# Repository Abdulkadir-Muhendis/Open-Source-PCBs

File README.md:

# Open-Source-PCBs
Open Source Printed Circuit Boards
----------------------------------

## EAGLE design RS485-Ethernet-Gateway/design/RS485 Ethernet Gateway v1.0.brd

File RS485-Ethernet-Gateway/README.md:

==========================================================================================================================================
# Next revision of this project is a part of upcoming crowdfunding campaign. Details [here](https://www.crowdsupply.com/domatic/getwired).
==========================================================================================================================================

## RS485 Module Family
This is ethernet gateway for RS485 (wired) MySensors nodes. It features ATmega328p MCU and ENC28J60 ethernet chip. SP485EE or similar IC is used as RS485 transceiver. It works on hardware serial to ensure more stability and to achieve higher baud rates.

The board itself is designed with having thermal issues in mind, since the ENC28J60 draws a lot of current. It features two 10-pin IDC sockets, one to connect external PCB with LEDs (Power, TX, RX, Error) and RESET button, and one for programming (MOSI, MISO, SCK, TX, RX, 5V, GND). Its size makes it case compatible with Raspberry Pi.

This work is a part of our [RS485 module system](https://www.openhardware.io/view/639/RS485-MCU-Module).

## Technical Specification
- ATmega328p MCU,
- ENC28J60 10Base-T ethernet controller,
- SP485EE for RS485 wired bus communication (working on hardware serial, pin 0 & 1),
- Shielded RJ45 socket with LEDs,
- 10-pin IDC socket for firmware updates and debugging,
- 10-pin IDC socket to connect external PCB with LEDs and a button (Power, TX, RX, Error, RESET),
- 5V and 3.3 V voltage regulators on board with large cooling pads,
- Power consumption < 2 W,
- Doubled outputs for RS485 bus connection (to connect the gateway easily in the middle of the bus).

## Q&A
We will place typical questions and answers here, if they occur.

## Firmware
- [Github](https://github.com/feanor-anglin/RS485)

## Our other RS485 boards
- [RS485 MCU Module](https://www.openhardware.io/view/639/RS485-MCU-Module)
- [RS485 2SSR Shield](https://www.openhardware.io/view/640/RS485-2SSR-Shield)
- [RS485 4RelayDin Shield](https://www.openhardware.io/view/641/RS485-4RelayDin-Shield)

## Other information
Copyright feanor-anglin (2018). Released under the [CERN Open Hardware Licence v1.2](http://ohwr.org/cernohl)

We develop Arduino compatibile hardware for wired home automation systems. If you like what we do and want us to keep going, please donate!

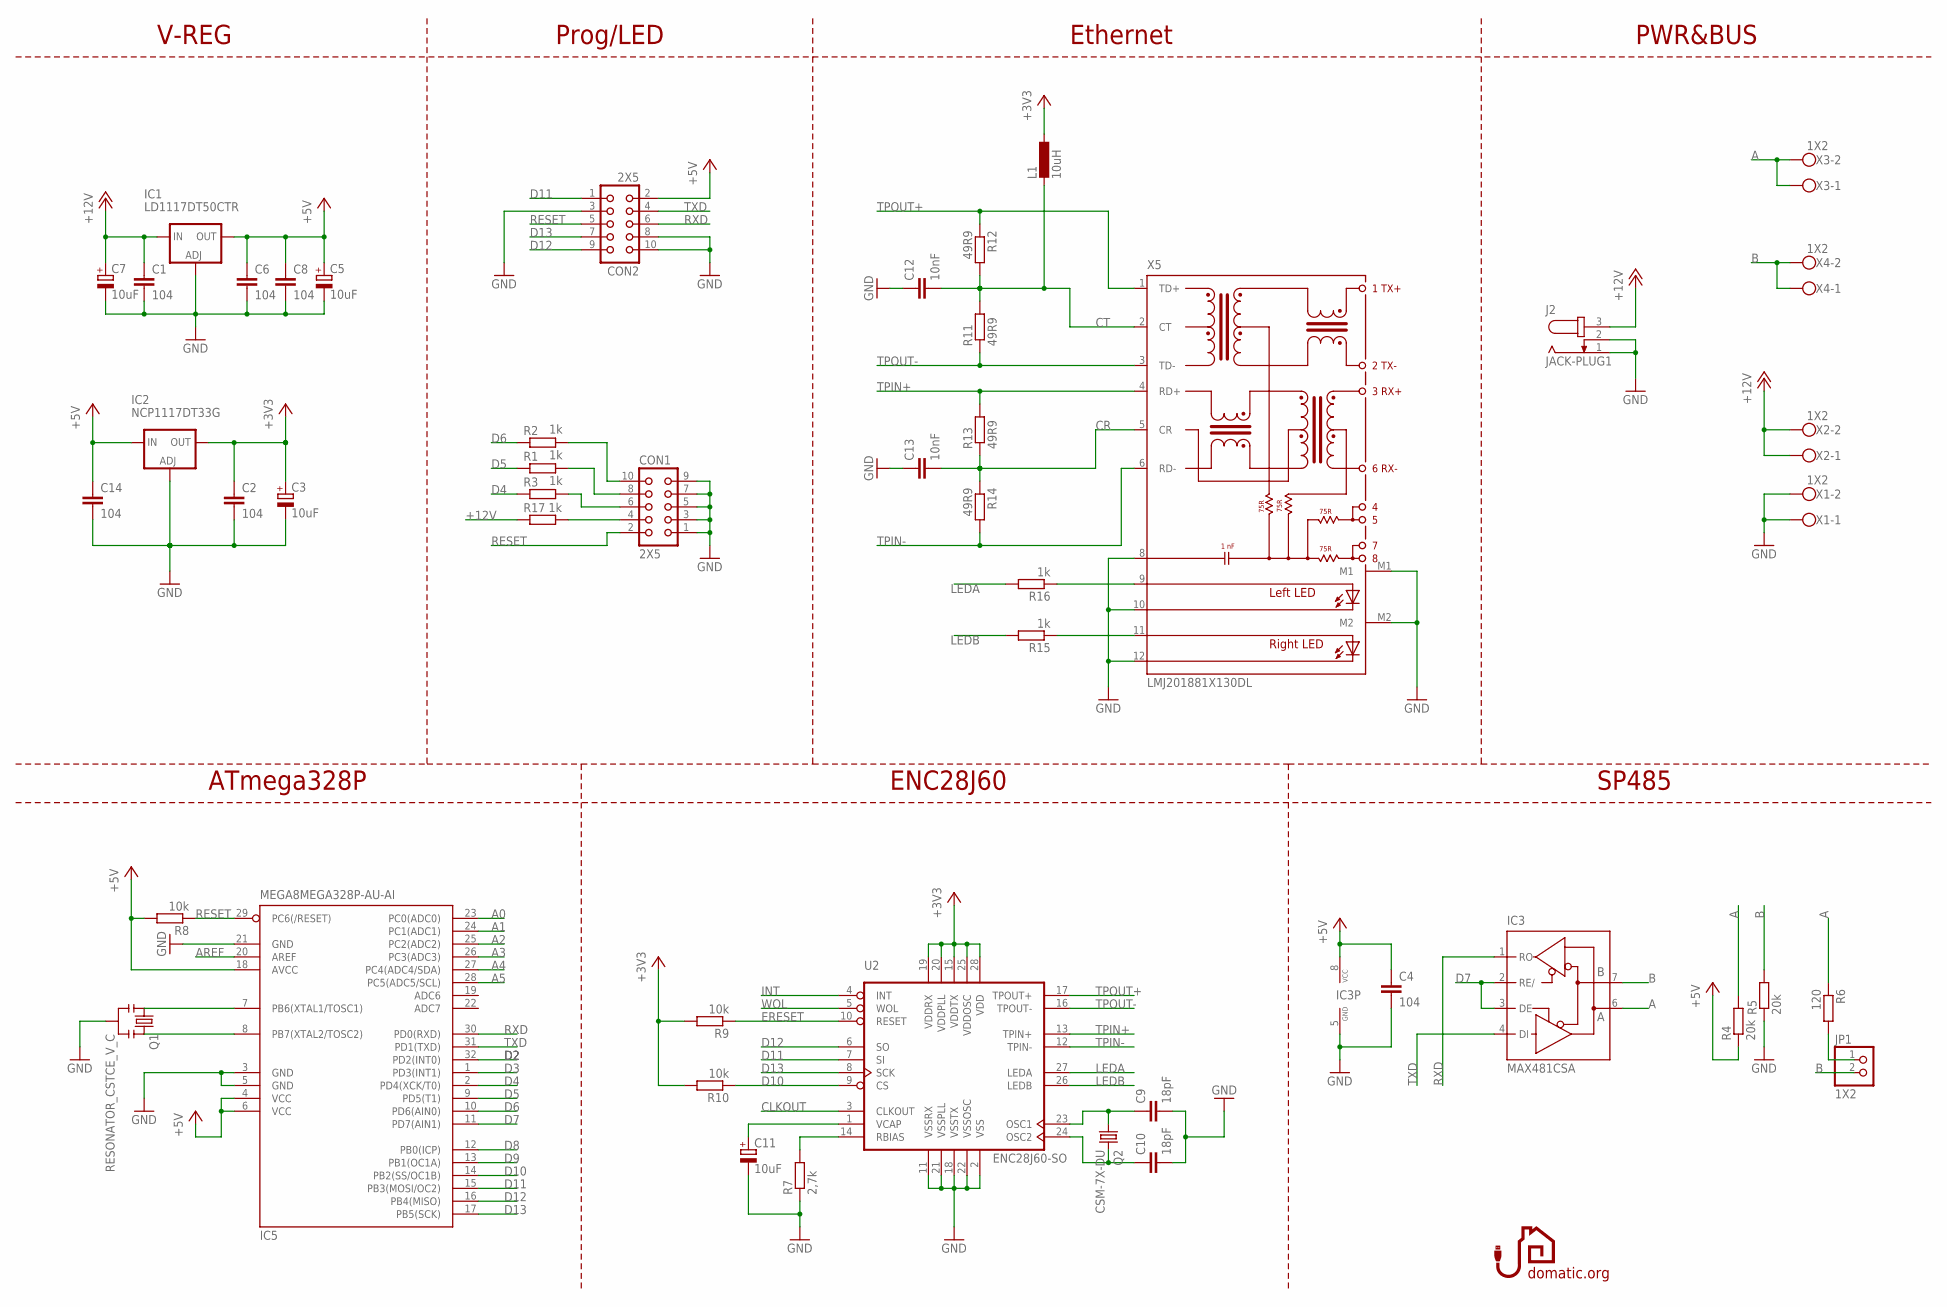
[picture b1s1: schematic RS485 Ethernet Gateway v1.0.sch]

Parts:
C1, C2, C4, C6, C8, C14: 104; C0603
C3, C5, C7, C11: 10uF; E2,5-7
C9, C10: 18pF; C0603
C12, C13: 10nF; C0603
CON1, CON2: 2X5; CON10L
IC1: LD1117DT50CTR; DPACK
IC2: NCP1117DT33G; DPACK
IC3: MAX481CSA; SO08
IC5: MEGA8MEGA328P-AU-AI; TQFP32-08
J2: JACK-PLUG1; SPC4078
JP1: 1X2; 1X02
L1: 10uH; C1608
Q1: RESONATOR_CSTCE_V_C; CSTCE_V_C
Q2: CSM-7X-DU
R1, R2, R3, R15, R16, R17: 1k; R0603
R4, R5: 20k; R0603
R6: 120; R0603
R7: 2,7k; R0603
R8, R9, R10: 10k; R0603
R11, R12, R13, R14: 49R9; R0603
U2: ENC28J60-SO; SO28W
X1, X2, X3, X4: 1X2; W237-102
X5: LMJ201881X130DL; LMJ20188X130

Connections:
+3V3: C2.1, C3.+, IC2.4 (OUT), L1.1, R9.2, R10.2, U2.15 (VDDTX), U2.19 (VDDRX), U2.20 (VDDPLL), U2.25 (VDDOSC), U2.28 (VDD)
+5V: C4.1, C5.+, C6.1, C8.1, C14.1, CON2.2, IC1.4 (OUT), IC2.3 (IN), IC3.8 (VCC), IC5.4 (VCC), IC5.6 (VCC), IC5.18 (AVCC), R4.1, R8.2
+12V: C1.1, C7.+, IC1.3 (IN), J2.3, R17.2, X2.1, X2.2
A: IC3.6 (A), R4.2, R6.1, X3.1, X3.2
A0: IC5.23 (PC0(ADC0))
A1: IC5.24 (PC1(ADC1))
A2: IC5.25 (PC2(ADC2))
A3: IC5.26 (PC3(ADC3))
A4: IC5.27 (PC4(ADC4/SDA))
A5: IC5.28 (PC5(ADC5/SCL))
AREF: IC5.20 (AREF)
B: IC3.7 (B), JP1.2, R5.2, X4.1, X4.2
CLKOUT: U2.3 (CLKOUT)
CR: C13.2, R13.1, R14.1, X5.5 (CR)
CT: C12.2, L1.2, R11.2, R12.2, X5.2 (CT)
D2: IC5.32 (PD2(INT0))
D3: IC5.1 (PD3(INT1))
D4: IC5.2 (PD4(XCK/T0)), R3.1
D5: IC5.9 (PD5(T1)), R1.1
D6: IC5.10 (PD6(AIN0)), R2.1
D7: IC3.2 (RE/), IC3.3 (DE), IC5.11 (PD7(AIN1))
D8: IC5.12 (PB0(ICP))
D9: IC5.13 (PB1(OC1A))
D10: IC5.14 (PB2(SS/OC1B)), R10.1, U2.9 (CS)
D11: CON2.1, IC5.15 (PB3(MOSI/OC2)), U2.7 (SI)
D12: CON2.9, IC5.16 (PB4(MISO)), U2.6 (SO)
D13: CON2.7, IC5.17 (PB5(SCK)), U2.8 (SCK)
ERESET: R9.1, U2.10 (RESET)
GND: C1.2, C2.2, C3.-, C4.2, C5.-, C6.2, C7.-, C8.2, C9.2, C10.2, C11.-, C12.1, C13.1, C14.2, CON1.1, CON1.3, CON1.5, CON1.7, CON1.9, CON2.3, CON2.8, CON2.10, IC1.1 (ADJ), IC2.1 (ADJ), IC3.5 (GND), IC5.3 (GND), IC5.5 (GND), IC5.21 (GND), J2.1, J2.2, Q1.GND, R5.1, R7.1, U2.2 (VSS), U2.11 (VSSRX), U2.18 (VSSTX), U2.21 (VSSPLL), U2.22 (VSSOSC), X1.1, X1.2, X5.8, X5.10, X5.12, X5.M1, X5.M2
INT: U2.4 (INT)
LEDA: R16.2, U2.27 (LEDA)
LEDB: R15.2, U2.26 (LEDB)
unnamed: JP1.1, R6.2
unnamed: CON1.6, R3.2
unnamed: CON1.8, R1.2
unnamed: C9.1, Q2.1, U2.23 (OSC1)
unnamed: CON1.10, R2.2
unnamed: C10.1, Q2.2, U2.24 (OSC2)
unnamed: R7.2, U2.14 (RBIAS)
unnamed: C11.+, U2.1 (VCAP)
unnamed: CON1.4, R17.1
unnamed: R16.1, X5.9
unnamed: R15.1, X5.11
unnamed: IC5.7 (PB6(XTAL1/TOSC1)), Q1.X1
unnamed: IC5.8 (PB7(XTAL2/TOSC2)), Q1.X2
RESET: CON1.2, CON2.5, IC5.29 (PC6(/RESET)), R8.1
RXD: CON2.6, IC3.1 (RO), IC5.30 (PD0(RXD))
TPIN+: R13.2, U2.13 (TPIN+), X5.4 (RD+)
TPIN-: R14.2, U2.12 (TPIN-), X5.6 (RD-)
TPOUT+: R12.1, U2.17 (TPOUT+), X5.1 (TD+)
TPOUT-: R11.1, U2.16 (TPOUT-), X5.3 (TD-)
TXD: CON2.4, IC3.4 (DI), IC5.31 (PD1(TXD))
WOL: U2.5 (WOL)

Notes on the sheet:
V-REG
Prog/LED
Ethernet
PWR&BUS
SP485
ENC28J60
ATmega328P

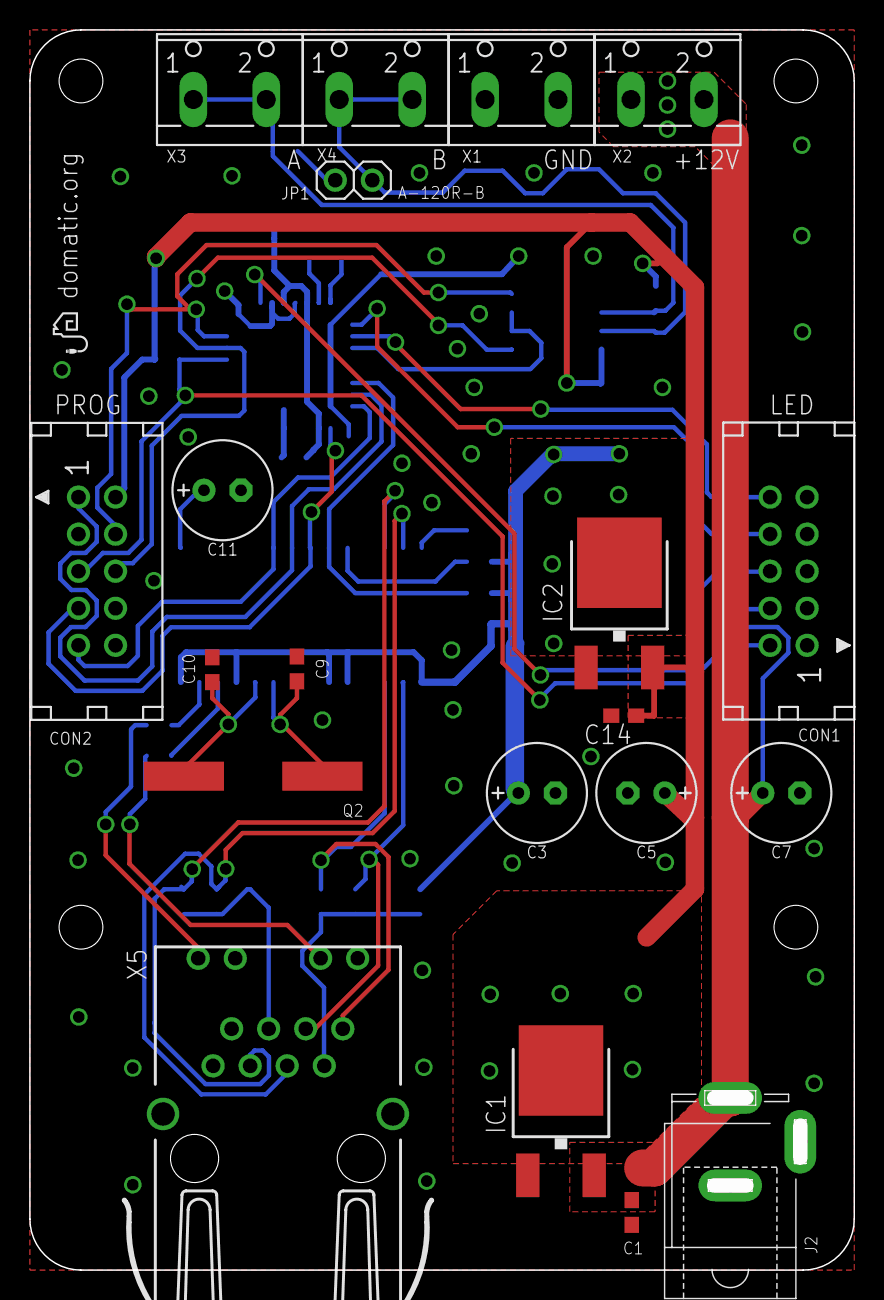
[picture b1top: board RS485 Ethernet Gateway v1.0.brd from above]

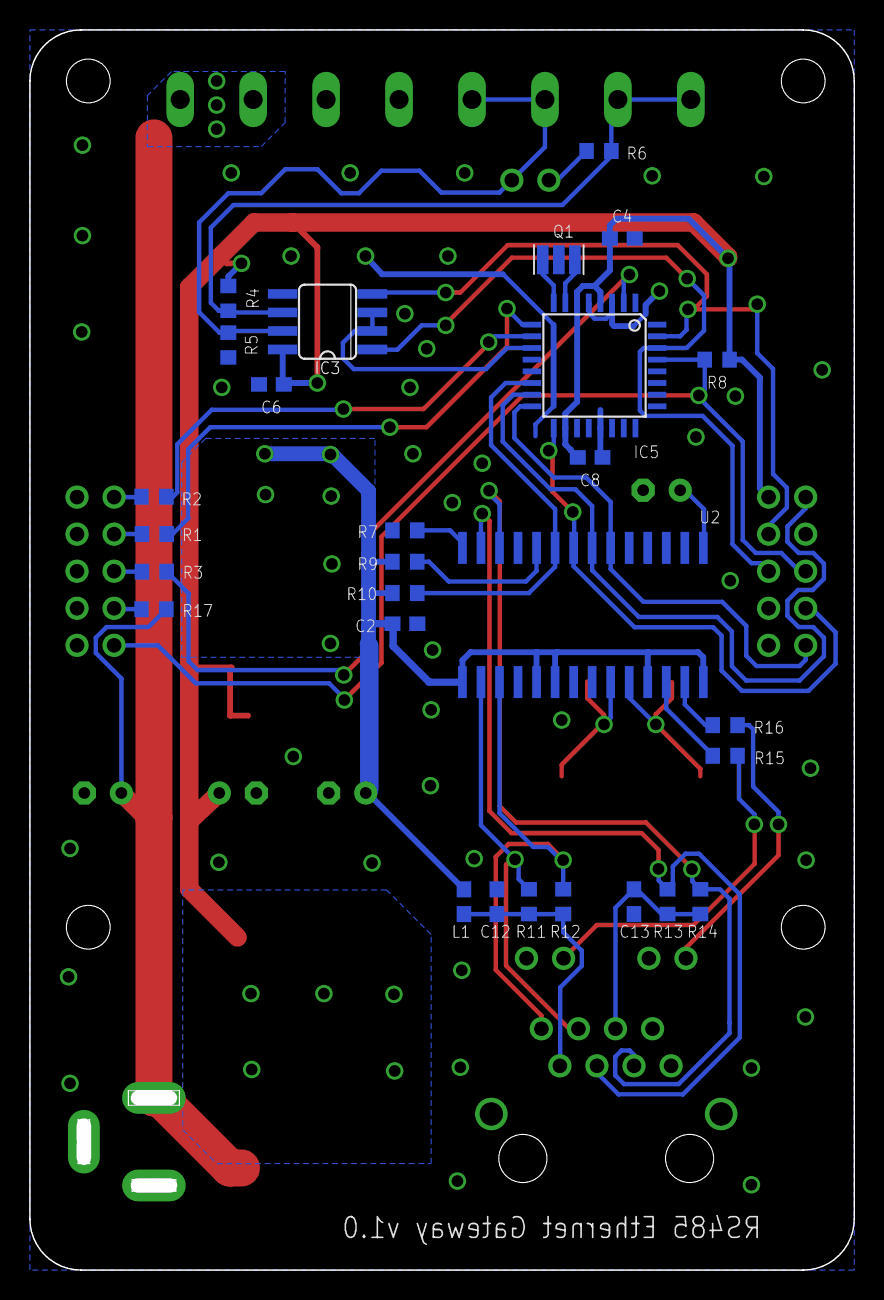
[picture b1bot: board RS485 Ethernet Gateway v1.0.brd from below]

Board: 2 copper layers, 56.5 x 85.0 mm, 49 parts (28 on the bottom side), 39 nets.

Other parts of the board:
U$3: LOGO2.5MMBEZNAZWY

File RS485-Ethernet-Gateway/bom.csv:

Qty,Value,Device,Package,Parts,Description,MF,MPN
2,2X5,CON10L,CON10L,"CON1, CON2",Connector,,
1,JACK-PLUG1,JACK-PLUG1,SPC4078,J2,DC power jack,,
1,1X2,PINHD-1X2,1X2,JP1,Pin header,,
4,W237-102,W237-102,W237-102,"X1, X2, X3, X4",Screw terminal,,
6,100n,C-EUC0603,C0603,"C1, C2, C4, C6, C8, C14",Capacitor,,
3,10k,R-EU_R0603,R0603,"R8, R9, R10",Resistor,,
2,10n,C-EUC0603,C0603,"C12, C13",Capacitor,,
4,10u,CPOL-EUE2.5-7,"E2,5-7","C3, C5, C7, C11",Polarized capacitor,,
1,10u,L-EU0603,C1608,L1,Inductor,,
1,120,R-EU_R0603,R0603,R6,Resistor,,
2,18p,C-EUC0603,C0603,"C9, C10",Capacitor,,
6,1k,R-EU_R0603,R0603,"R1, R2, R3, R15, R16, R17",Resistor,,
1,"2,7k",R-EU_R0603,R0603,R7,Resistor,,
2,20k,R-EU_R0603,R0603,"R4, R5",Resistor,,
4,"49,9",R-EU_R0603,R0603,"R11, R12, R13, R14",Resistor,,
1,CSM-7X-DU,CSM-7X-DU,CSM-7X-DU,Q2,Resonator 25 MHz,,
1,ENC28J60-SO,ENC28J60-SO,SO28W,U2,Ethernet contoller,,
1,LD1117DT50CTR,LD117ADT50TR,DPACK,IC1,Low Dropout Regulator,,
1,LMJ201881X130DL,LMJ201881X130DL,LMJ20188X130,X5,RJ45 Socket,,
1,SP485EE,MAX481CSA,SO08,IC3,RS485 Transeiver,,
1,MEGA328P-AU,MEGA8MEGA328P-AU-AI,TQFP32-08,IC5,Microcontroller,,
1,NCP1117DT33G,LD117ADT33TR,DPACK,IC2,Low Dropout Regulator,,
1,CSTCE16M0V53C-R0,RESONATOR_CSTCE_V_C,CSTCE_V_C,Q1,Resonator 16 MHz,,

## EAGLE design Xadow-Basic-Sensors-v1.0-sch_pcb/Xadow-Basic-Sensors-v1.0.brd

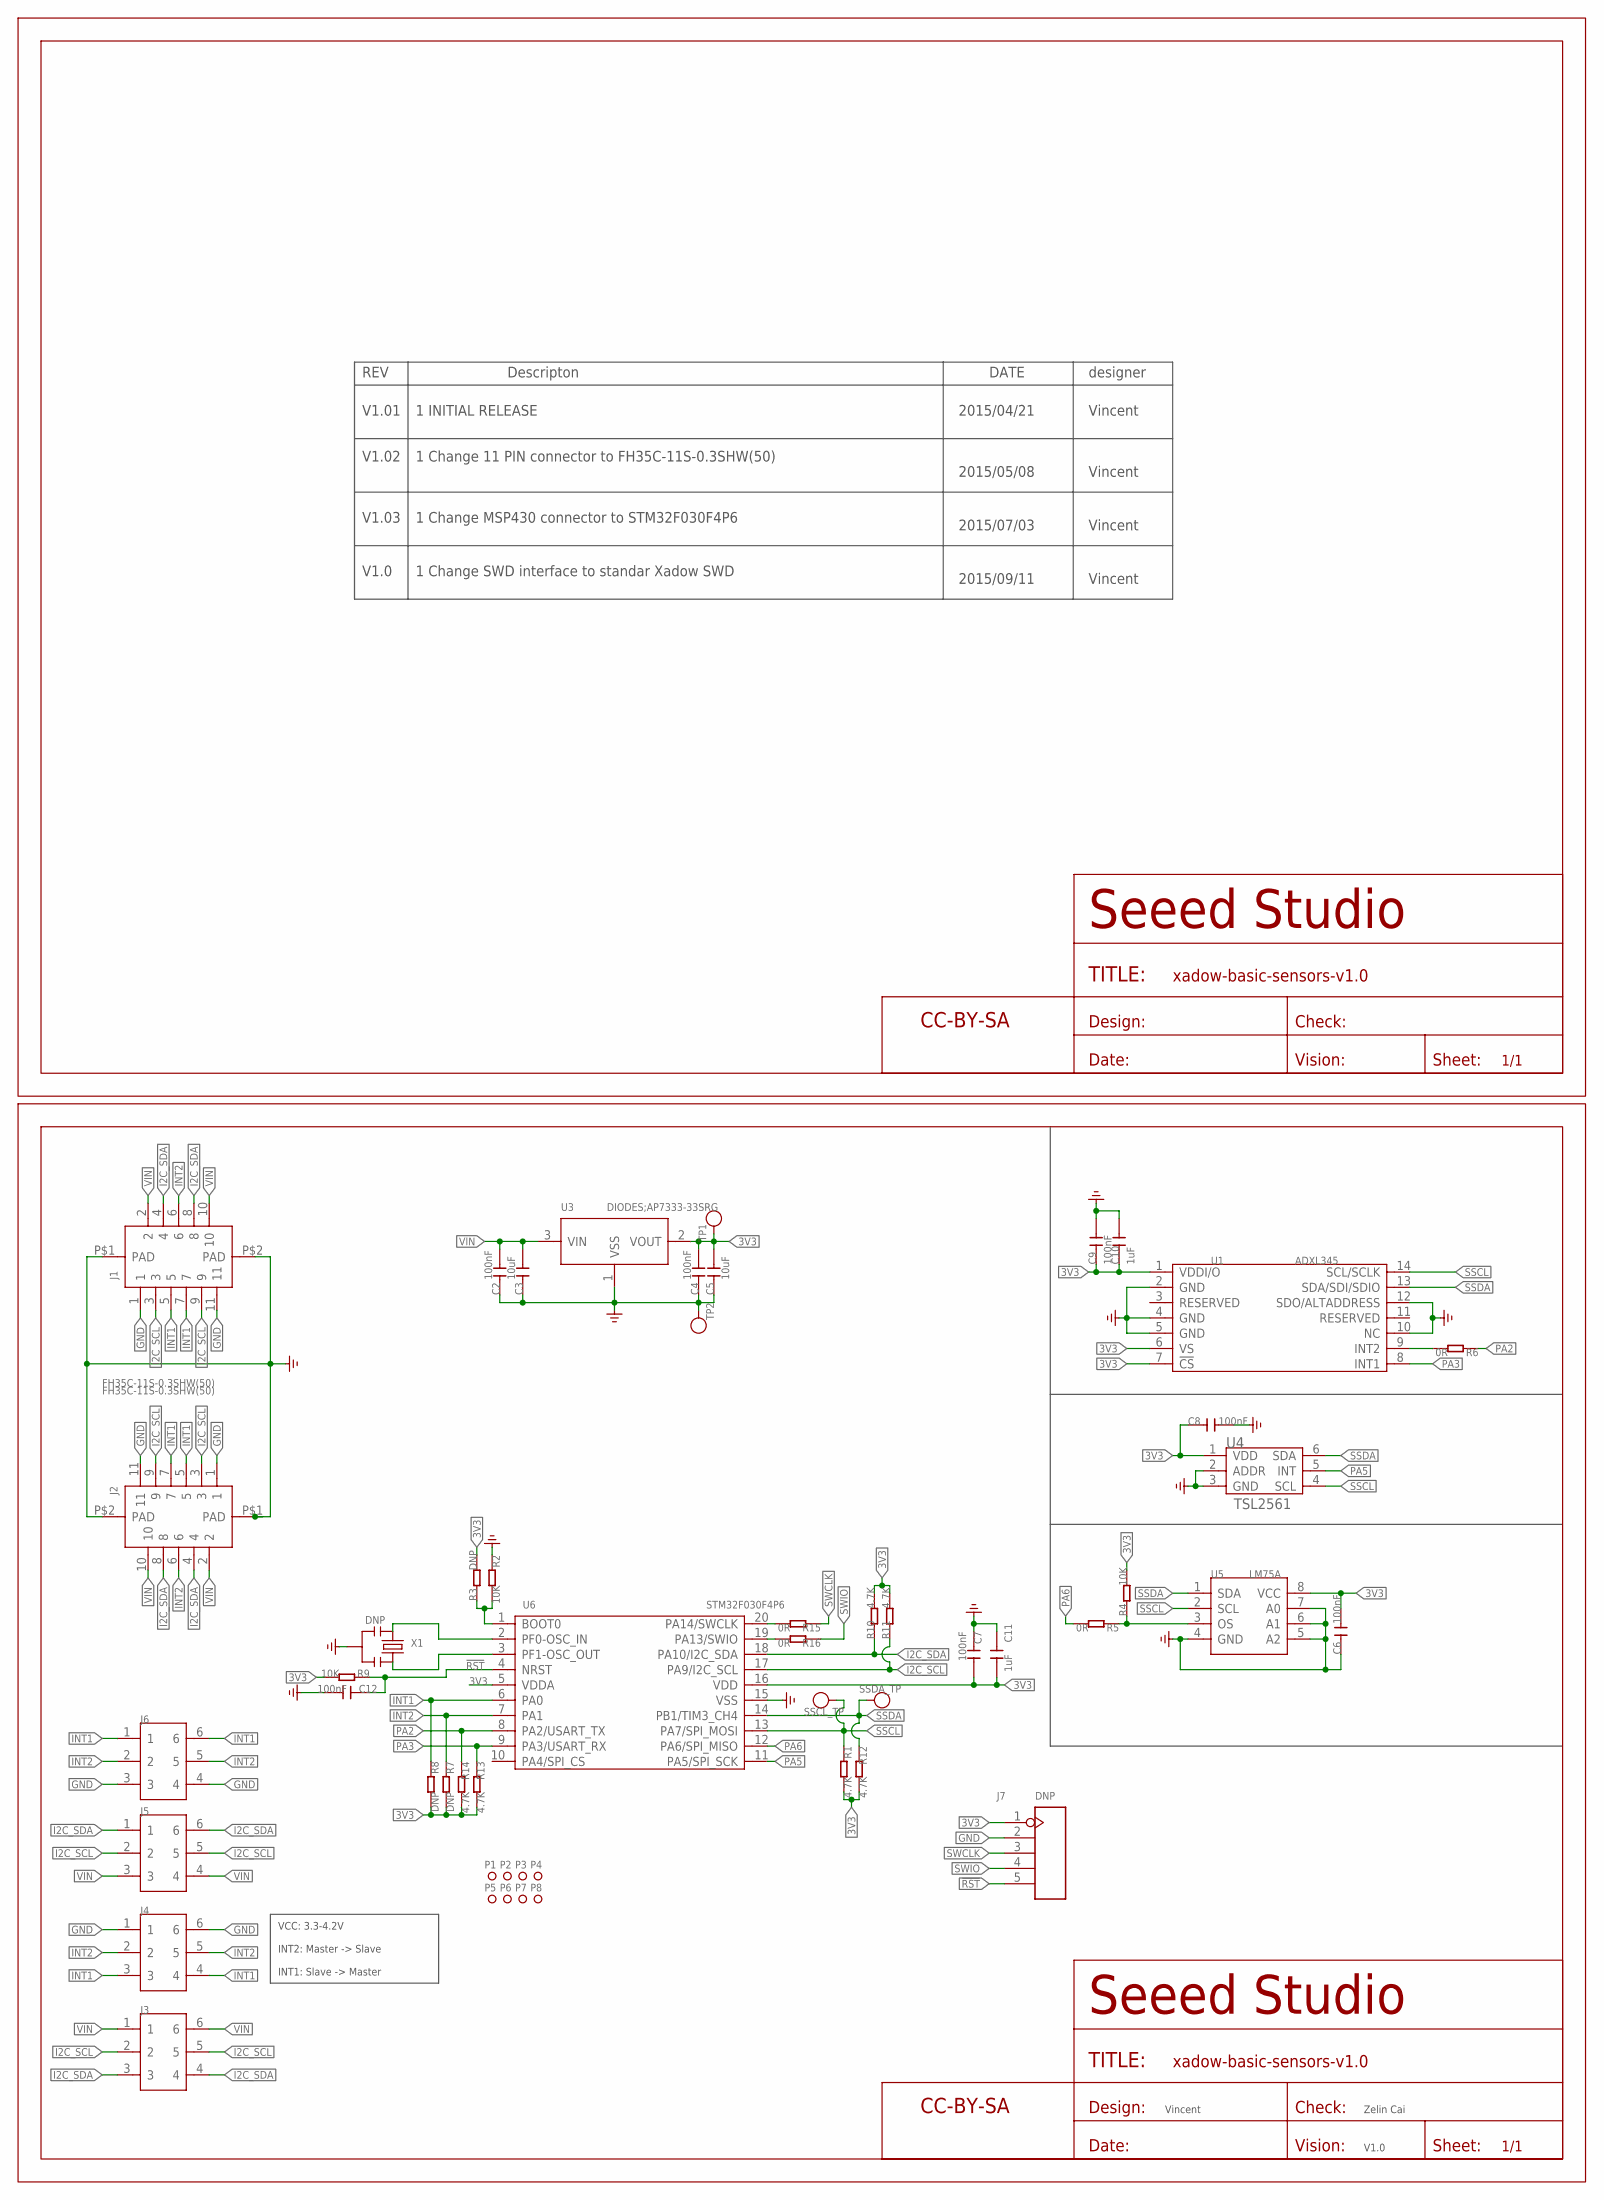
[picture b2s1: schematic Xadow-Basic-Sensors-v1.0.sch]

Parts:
C2, C4, C6, C7, C8, C9, C12: 100nF; C0402
C3, C5: 10uF; C0603
C10, C11: 1uF; C0402
FR1: SEEEDSTUDIO-OPEN-SCH-FRAME; SEEEDSTUDIO-PCB-FRAME
J1, J2: FH35C-11S-0.3SHW(50); FPC11-SMD-0.3(FH35C)
J3: HEADER6_S3; 6P-DIP-2_S3
J4, J6: HEADER6_ROUND; 6P-DIP-2_ROUND
J5: HEADER6; 6P-DIP-2
J7: DNP; H5-SMD-2.0-TEST
P1, P2, P3, P4, P5, P6, P7, P8: MARK-1.0'ANNULAR'; ROUND-MARK-1.0
R1, R10, R11, R12, R13, R14: 4.7K; R0402
R2, R4, R9: 10K; R0402
R3, R7, R8: DNP; R0402
R5, R6, R15, R16: 0R; R0402
SSCL_TP: TEST-POINT'4545'; TP-D45MIL
SSDA_TP: TEST-POINT'4545'; TP-D45MIL
TP1, TP2: TEST-POINT'4545'; TP-D45MIL
U1: ADXL345; LGA14
U3: DIODES;AP7333-33SRG; SOT-23
U4: TSL2561; TMB-6
U5: LM75A; TSSOP8-0.65-3X3MM
U6: STM32F030F4P6; TSSOP20-0.65-6.5X4.4MM
U$2: SEEEDSTUDIO-OPEN-SCH-FRAME; SEEEDSTUDIO-PCB-FRAME
X1: DNP; RESONATOR3-SMD-3.6X1.3X0.8MM

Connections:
3V3: C4.2, C5.2, C6.2, C7.2, C8.1, C9.1, C10.1, C11.2, J7.1, R1.2, R3.2, R4.2, R7.2, R8.2, R9.2, R10.2, R11.2, R12.2, R13.2, R14.2, TP1.T, U1.1 (VDDI/O), U1.6 (VS), U1.7 (!CS), U3.2 (VOUT), U4.1 (VDD), U5.8 (VCC), U6.5 (VDDA), U6.16 (VDD)
!RST: C12.1, J7.5, R9.1, U6.4 (NRST)
GND: C2.1, C3.1, C4.1, C5.1, C6.1, C7.1, C8.2, C9.2, C10.2, C11.1, C12.2, J1.1, J1.11, J1.P$1 (PAD), J1.P$2 (PAD), J2.1, J2.11, J2.P$1 (PAD), J2.P$2 (PAD), J4.1, J4.6, J6.3, J6.4, J7.2, R2.1, TP2.T, U1.2 (GND), U1.4 (GND), U1.5 (GND), U1.10 (NC), U1.12 (SDO/ALTADDRESS), U3.1 (VSS), U4.2 (ADDR), U4.3 (GND), U5.4 (GND), U5.5 (A2), U5.6 (A1), U5.7 (A0), U6.15 (VSS), X1.2
I2C_SCL: J1.3, J1.9, J2.3, J2.9, J3.2, J3.5, J5.2, J5.5, R11.1, U6.17 (PA9/I2C_SCL)
I2C_SDA: J1.4, J1.8, J2.4, J2.8, J3.3, J3.4, J5.1, J5.6, R10.1, U6.18 (PA10/I2C_SDA)
INT1: J1.5, J1.7, J2.5, J2.7, J4.3, J4.4, J6.1, J6.6, R8.1, U6.6 (PA0)
INT2: J1.6, J2.6, J4.2, J4.5, J6.2, J6.5, R7.1, U6.7 (PA1)
unnamed: R6.2, U1.9 (INT2)
unnamed: U6.2 (PF0-OSC_IN), X1.3
unnamed: R4.1, R5.1, U5.3 (OS)
unnamed: U6.3 (PF1-OSC_OUT), X1.1
unnamed: R2.2, R3.1, U6.1 (BOOT0)
unnamed: R15.2, U6.20 (PA14/SWCLK)
unnamed: R16.2, U6.19 (PA13/SWIO)
PA2: R6.1, R14.1, U6.8 (PA2/USART_TX)
PA3: R13.1, U1.8 (INT1), U6.9 (PA3/USART_RX)
PA5: U4.5 (INT), U6.11 (PA5/SPI_SCK)
PA6: R5.2, U6.12 (PA6/SPI_MISO)
SSCL: R1.1, SSCL_TP.T, U1.14 (SCL/SCLK), U4.4 (SCL), U5.2 (SCL), U6.13 (PA7/SPI_MOSI)
SSDA: R12.1, SSDA_TP.T, U1.13 (SDA/SDI/SDIO), U4.6 (SDA), U5.1 (SDA), U6.14 (PB1/TIM3_CH4)
SWCLK: J7.3, R15.1
SWIO: J7.4, R16.1
VIN: C2.2, C3.2, J1.2, J1.10, J2.2, J2.10, J3.1, J3.6, J5.3, J5.4, U3.3 (VIN)

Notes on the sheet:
Vincent
Zelin Cai
V1.0
INT1: Slave -> Master
INT2: Master -> Slave
VCC: 3.3-4.2V
REV
Descripton
DATE
designer
V1.01
1 INITIAL RELEASE
V1.02
1 Change 11 PIN connector to FH35C-11S-0.3SHW(50)
2015/04/21
2015/05/08
V1.03
2015/07/03
1 Change MSP430 connector to STM32F030F4P6
2015/09/11
1 Change SWD interface to standar Xadow SWD

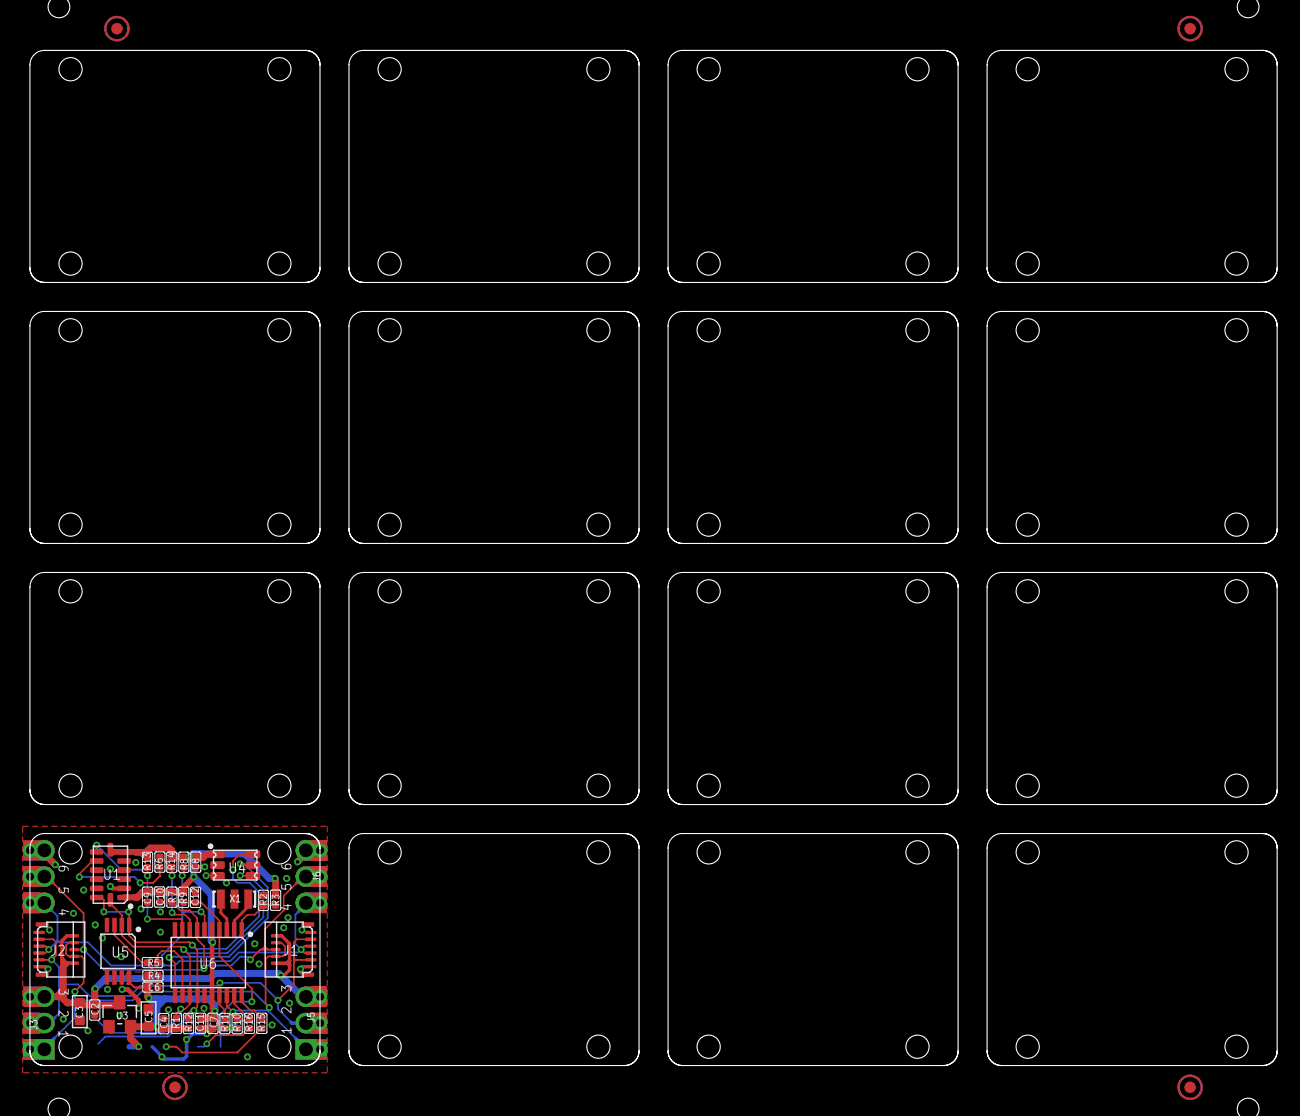
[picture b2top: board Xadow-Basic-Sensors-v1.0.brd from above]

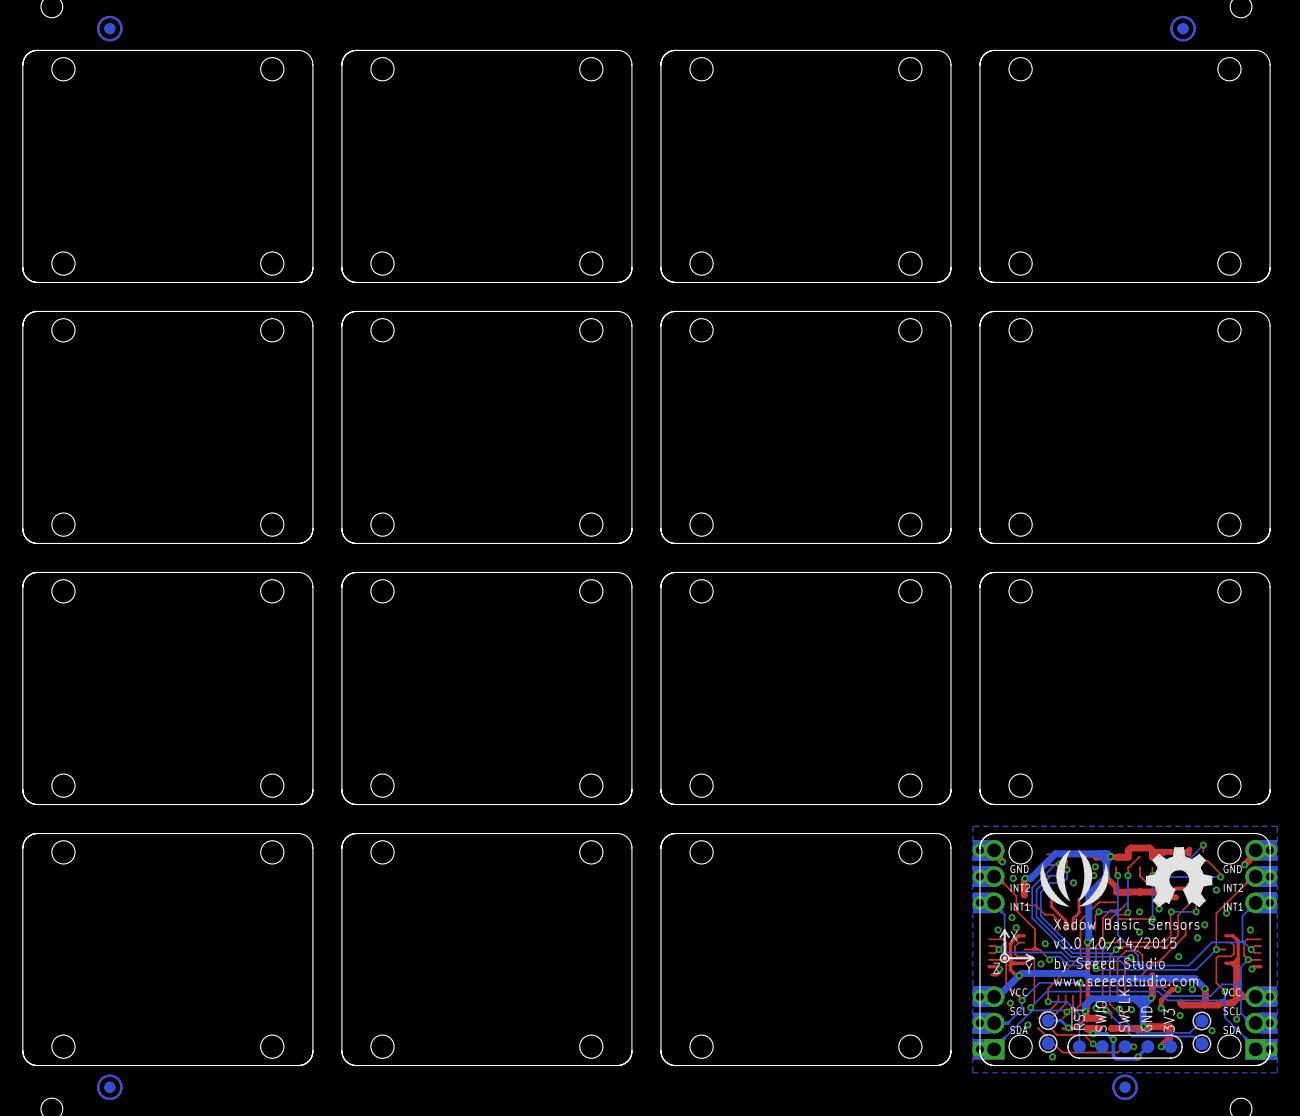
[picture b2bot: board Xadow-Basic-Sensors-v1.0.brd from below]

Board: 2 copper layers, 109.2 x 88.9 mm, 56 parts (11 on the bottom side), 23 nets.

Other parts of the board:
U$18: OSHW_FILLX200_NOTEXT
U$20: SEEED-SILK-280*268MIL

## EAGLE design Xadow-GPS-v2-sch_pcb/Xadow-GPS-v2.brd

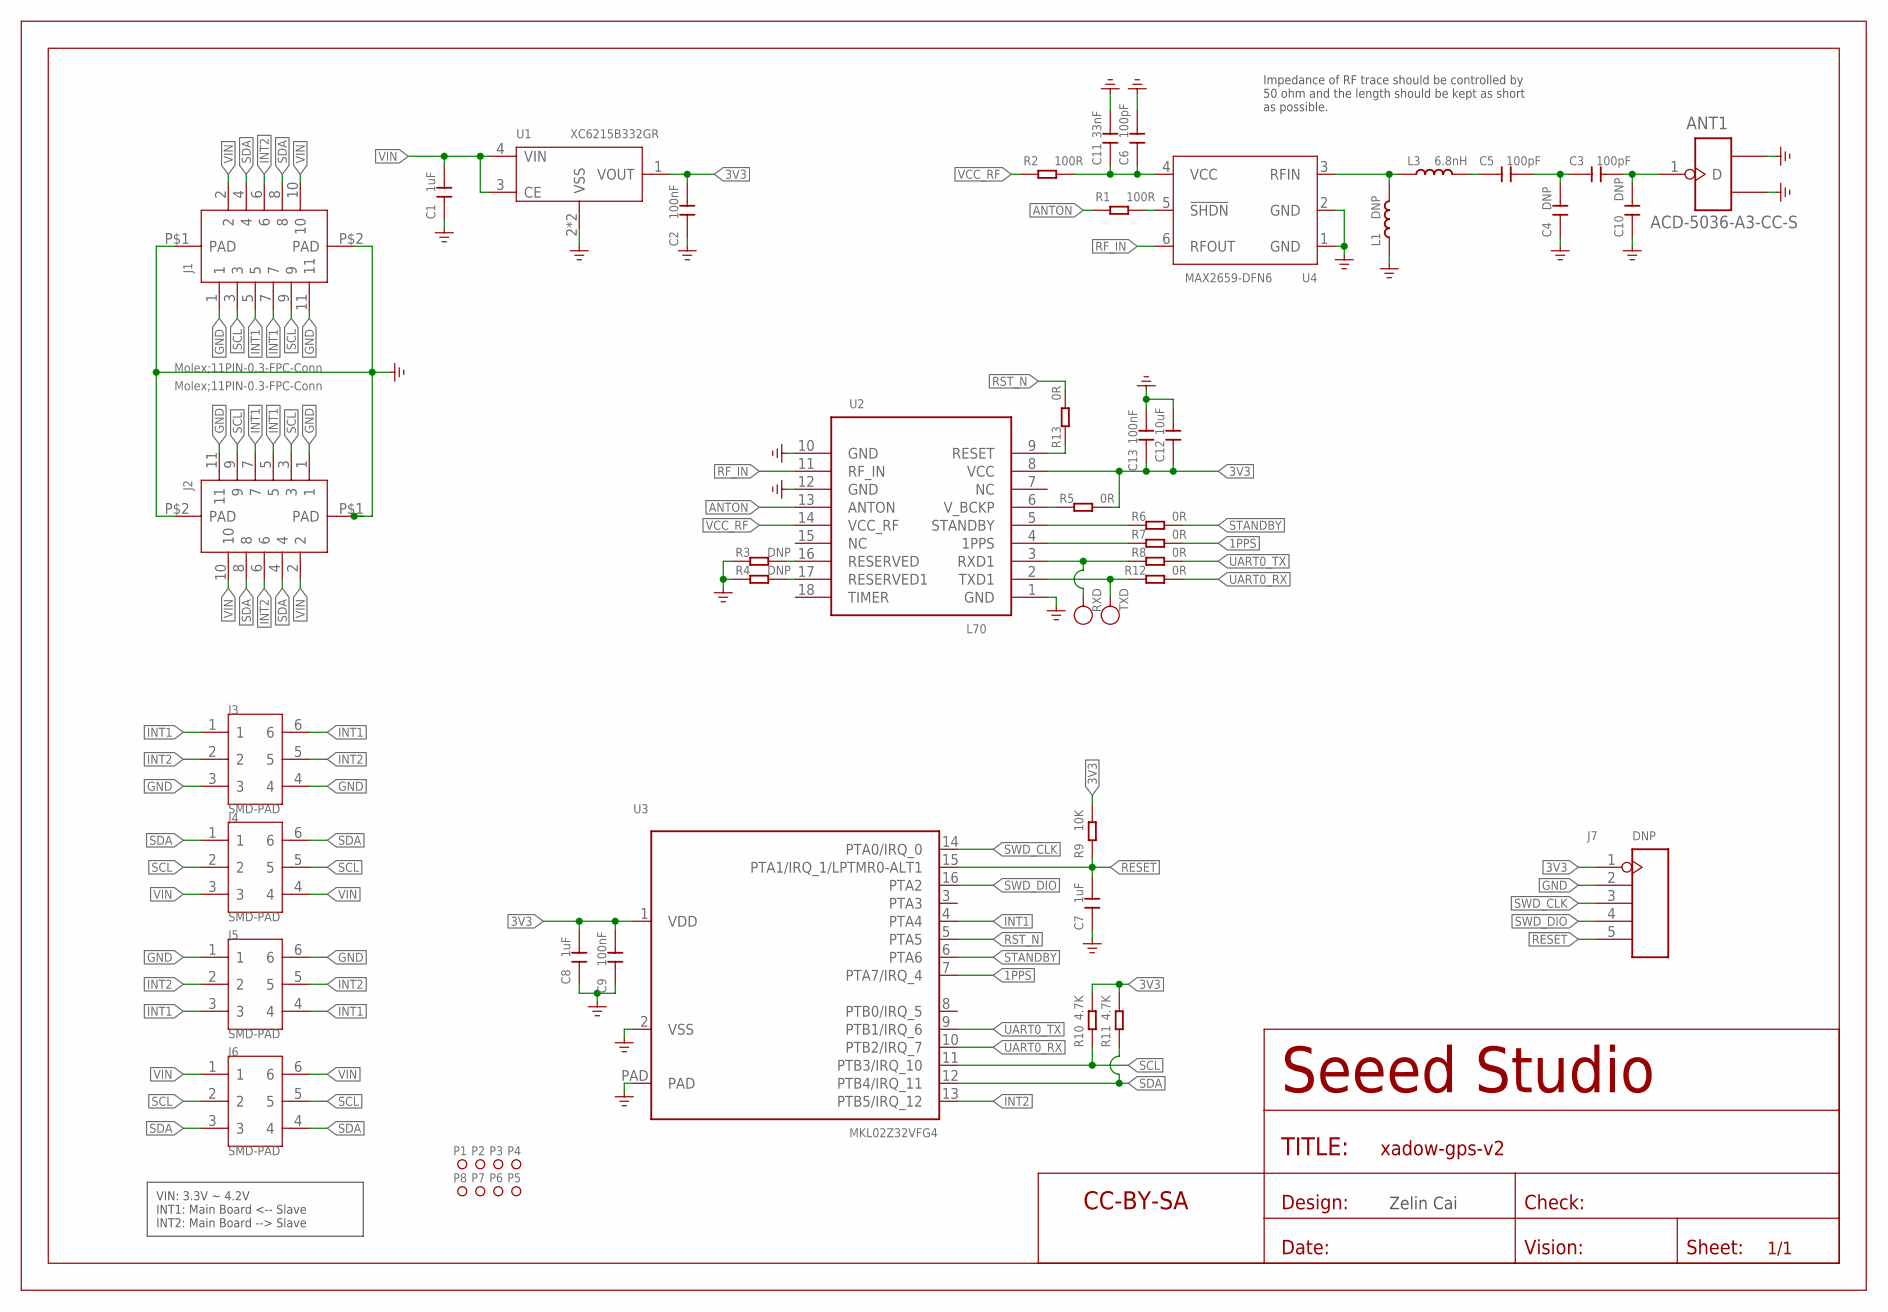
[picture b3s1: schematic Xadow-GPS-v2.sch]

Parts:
ANT1: ACD-5036-A3-CC-S; ANT3-SMD-5.2X3.7X0.7MM
C1, C8: 1uF; C0402
C2, C9, C13: 100nF; C0201
C3, C5, C6: 100pF; C0201
C4, C10: DNP; C0201
C7: 1uF; C0201
C11: 33nF; C0201
C12: 10uF; C0402
FR: PAGE1; SEEEDSTUDIO-PCB-FRAME
J1, J2: Molex;11PIN-0.3-FPC-Conn; FPC11-SMD-0.3(FH35C)
J3, J5: SMD-PAD; 6P-DIP-2_ROUND
J4: SMD-PAD; 6P-DIP-2
J6: SMD-PAD; 6P-DIP-2_S3
J7: DNP; H5-SMD-2.0-TEST
L1: DNP; L0201
L3: 6.8nH; L0201
P1, P2, P3, P4, P5, P6, P7, P8: MRK; ROUND-MARK-1.0
R1, R2: 100R; R0201
R3, R4: DNP; R0201
R5, R6, R7, R8, R12, R13: 0R; R0201
R9: 10K; R0201
R10, R11: 4.7K; R0201
RXD: RXD; TP-D45MIL
TXD: TXD; TP-D45MIL
U1: XC6215B332GR; USP4-0.6-1.2X1.6MM
U2: L70; LGA18-1.1-9.7X10.1X2.5MM
U3: MKL02Z32VFG4; QFN16G-0.5-3X3MM
U4: MAX2659-DFN6; DFN6-0.5-1.5X1.2X0.72MM

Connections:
1PPS: R7.1, U3.7 (PTA7/IRQ_4)
3V3: C2.2, C8.2, C9.2, C12.1, C13.1, J7.1, R5.1, R9.2, R10.2, R11.2, U1.1 (VOUT), U2.8 (VCC), U3.1 (VDD)
!RESET: C7.2, J7.5, R9.1, U3.15 (PTA1/IRQ_1/LPTMR0-ALT1)
ANTON: R1.2, U2.13 (ANTON)
GND: ANT1.2 (GND1), ANT1.3 (GND2), C1.1, C2.1, C4.1, C6.2, C7.1, C8.1, C9.1, C10.1, C11.2, C12.2, C13.2, J1.1, J1.11, J1.P$1 (PAD), J1.P$2 (PAD), J2.1, J2.11, J2.P$1 (PAD), J2.P$2 (PAD), J3.3, J3.4, J5.1, J5.6, J7.2, L1.1, R3.2, R4.2, U1.2 (VSS), U1.PAD (VSS), U2.1 (GND), U2.10 (GND), U2.12 (GND), U3.2 (VSS), U3.PAD, U4.1 (GND), U4.2 (GND)
INT1: J1.5, J1.7, J2.5, J2.7, J3.1, J3.6, J5.3, J5.4, U3.4 (PTA4)
INT2: J1.6, J2.6, J3.2, J3.5, J5.2, J5.5, U3.13 (PTB5/IRQ_12)
unnamed: C3.1, C4.2, C5.2
unnamed: ANT1.1 (D), C3.2, C10.2
unnamed: L1.2, L3.1, U4.3 (RFIN)
unnamed: C5.1, L3.2
unnamed: R1.1, U4.5 (!SHDN)
unnamed: C6.1, C11.1, R2.1, U4.4 (VCC)
unnamed: R3.1, U2.16 (RESERVED)
unnamed: R4.1, U2.17 (RESERVED1)
unnamed: R5.2, U2.6 (V_BCKP)
unnamed: R6.2, U2.5 (STANDBY)
unnamed: R7.2, U2.4 (1PPS)
unnamed: R13.2, U2.9 (RESET)
RF_IN: U2.11 (RF_IN), U4.6 (RFOUT)
RST_N: R13.1, U3.5 (PTA5)
RXD1: R8.2, RXD.T, U2.3 (RXD1)
SCL: J1.3, J1.9, J2.3, J2.9, J4.2, J4.5, J6.2, J6.5, R10.1, U3.11 (PTB3/IRQ_10)
SDA: J1.4, J1.8, J2.4, J2.8, J4.1, J4.6, J6.3, J6.4, R11.1, U3.12 (PTB4/IRQ_11)
STANDBY: R6.1, U3.6 (PTA6)
SWD_CLK: J7.3, U3.14 (PTA0/IRQ_0)
SWD_DIO: J7.4, U3.16 (PTA2)
TXD1: R12.2, TXD.T, U2.2 (TXD1)
UART0_RX: R12.1, U3.10 (PTB2/IRQ_7)
UART0_TX: R8.1, U3.9 (PTB1/IRQ_6)
VCC_RF: R2.2, U2.14 (VCC_RF)
VIN: C1.2, J1.2, J1.10, J2.2, J2.10, J4.3, J4.4, J6.1, J6.6, U1.3 (CE), U1.4 (VIN)

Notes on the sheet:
Zelin Cai
Impedance of RF trace should be controlled by 50 ohm and the length should be kept as short as possible.
VIN: 3.3V ~ 4.2V INT1: Main Board <-- Slave INT2: Main Board --> Slave

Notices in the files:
parts and their libraries:
moudle-new: This work is licensed under the Creative Commons Attribution 4.0 International License.
To view a copy of this license,visit:
http://creativecommons.org/licenses/by-sa/4.0
moudle-new: CC-BY-SA
